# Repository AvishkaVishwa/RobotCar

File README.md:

# 🤖 Sumo Robot – ESP32 Upgrade Edition

> ⚡ A complete redesign and performance upgrade of my original ESP32-based 2-wheel robot — now featuring 4-wheel differential drive, dual motor drivers, enhanced sensing, and a **custom-designed 2-layer PCB** for clean, robust competition performance.

---
## 🏅 Awards & Achievements

> 🥈 **2nd Place – University Robotics Competition**  
> My previous 2-wheel ESP32-based robot won **2nd place** in a university competition.  
> 🎯 **Challenge Objective:** Remove the maximum number of boxes from a designated area as fast as possible.  
> 💡 The robot autonomously navigated, detected, and pushed objects while avoiding boundaries.  
>
> This new 4-wheel version builds on that success with:
> - A custom PCB for higher stability and motor control
> - Dual-mode (Autonomous + BLE Manual) operation
> - Improved PD-based line tracking and obstacle avoidance
> - Real-time scanning with servo-driven sensors

## 🔄 Evolution of the Project

| Original Prototype                    | 🚀 **Upgraded Version**                             |
|--------------------------------------|----------------------------------------------------|
| ESP32 on protoboard                  | ESP32 DevKit (38-pin) on custom 2-layer PCB        |
| 2-wheel drive with single TB6612FNG  | 4-wheel drive using dual TB6612FNG drivers         |
| Breadboard wiring                    | Professionally routed and labeled PCB in KiCad     |
| 1 ultrasonic + 2 IR sensors          | 2 ultrasonic + 3 IR sensors                        |
| Basic C firmware                     | Modular, RTOS-based firmware with **ESP-IDF**      |

### 🔧 The Current design 

| Old Design |
|------------|

---

## ⚙ Hardware Overview

### 📍 ESP32 GPIO Mapping

| Feature             | GPIOs                            | Description                      |
|---------------------|-----------------------------------|----------------------------------|
| **Motor Driver 1**  | AIN1: 13, AIN2: 14                | Left Front Motor Direction       |
|                     | BIN1: 12, BIN2: 27                | Left Rear Motor Direction        |
|                     | PWMA: 26, PWMB: 25                | Speed Control (PWM)              |
| **Motor Driver 2**  | AIN1: 33, AIN2: 32                | Right Front Motor Direction      |
|                     | BIN1: 19, BIN2: 18                | Right Rear Motor Direction       |
|                     | PWMA: 23, PWMB: 22                | Speed Control (PWM)              |
| **STBY Pin**        | 15                                | Keep HIGH to enable motors       |
| **IR Sensors**      | 34, 35, 39                        | Left, Center, Right (input only) |
| **Ultrasonic**      | TRIG1: 5, ECHO1: 36               | Front sensor                     |
|                     | TRIG2: 4, ECHO2: 21               | Side sensor                      |
| **Servos**          | SERVO1: 2, SERVO2: 17             | Optional (PWM outputs)           |

---

## 📐 PCB Design (KiCad)

This upgrade features a fully custom 2-layer PCB:
- Dual motor driver breakout with decoupling capacitors
- LM2596 buck converter (12V to 5V)
- Pull-up/pull-down resistors for boot-safe ESP32 pins
- Clear silk labels for servo, IR, ultrasonic, and power pins

### PCB Gallery

#### 📘 Schematic View

#### 🧵 Routed View

#### 📐 2D Top View

#### 🧱 3D Render

---

## ⚙ Software Architecture

Built using **ESP-IDF + FreeRTOS**, the firmware is modular and real-time.

| Module           | Function                                      |
|------------------|-----------------------------------------------|
|    `main.c`      | Set motor direction and PWM speed             |
|                  | Read ultrasonic and IR sensor values          |
|                  | Control servo angles (expandable feature)     |
|                  | Main loop with attack, avoid, search routines |

---

## 🔧 Setup & Flashing

### Prerequisites
- ESP-IDF environment
- ESP32 DevKit (38-pin)
- 12V battery + USB cable

### Flash Instructions

git clone https://github.com/AvishkaVishwa/RobotCar.git
cd robot-project
idf.py build
idf.py -p /dev/ttyUSB0 flash
idf.py monitor

---

## 📹 Videos & Demos

> 🎥 Want to see it in action?
> I’ve recorded videos of both the prototype and the upgraded robot performing edge detection, object pushing, and spiral search.

📌  <video src ="https://github.com/user-attachments/assets/8567fc42-a18b-4fbb-b69a-60d1c5493e56"></video>

📌 Here Is a test of the car with New PCB, I m still doing some modifications to this....😁 And i'm controlling the car with Bluetooth using the mobile phone.
    <video src ="https://github.com/user-attachments/assets/c9dc8e6a-7c8a-46cb-9330-15c2b81f15a4"></video>
---

## 📚 What This Project Shows

* Embedded firmware development with **ESP-IDF**
* **Custom PCB design** (routing, power, protection, labeling)
* Real-time autonomous behavior
* Motor control using **PWM & H-bridges**
* Sensor fusion: ultrasonic + IR edge detection
* Full-stack development from electronics to software

---

## 🤝 Contributions Welcome

Feel free to fork or suggest ideas such as:

* PID control integration
* Remote control override via WiFi
* OLED display for system status

---
---

## 🎉 Special Thanks to PCBWay

<p align="center">
  
</p>

I would like to give a huge shoutout and sincere thanks to **[PCBWay](https://www.pcbway.com/)** for sponsoring the PCB fabrication of this project!

The **build quality, silkscreen clarity, via precision, and copper finish** exceeded expectations. PCBWay’s service was fast, professional, and extremely helpful throughout the production process.

This project wouldn’t have been possible without their generous support. If you’re looking to manufacture professional-grade PCBs at an affordable price, I highly recommend checking them out.

🔗 [Visit PCBWay →](https://www.pcbway.com/)

---

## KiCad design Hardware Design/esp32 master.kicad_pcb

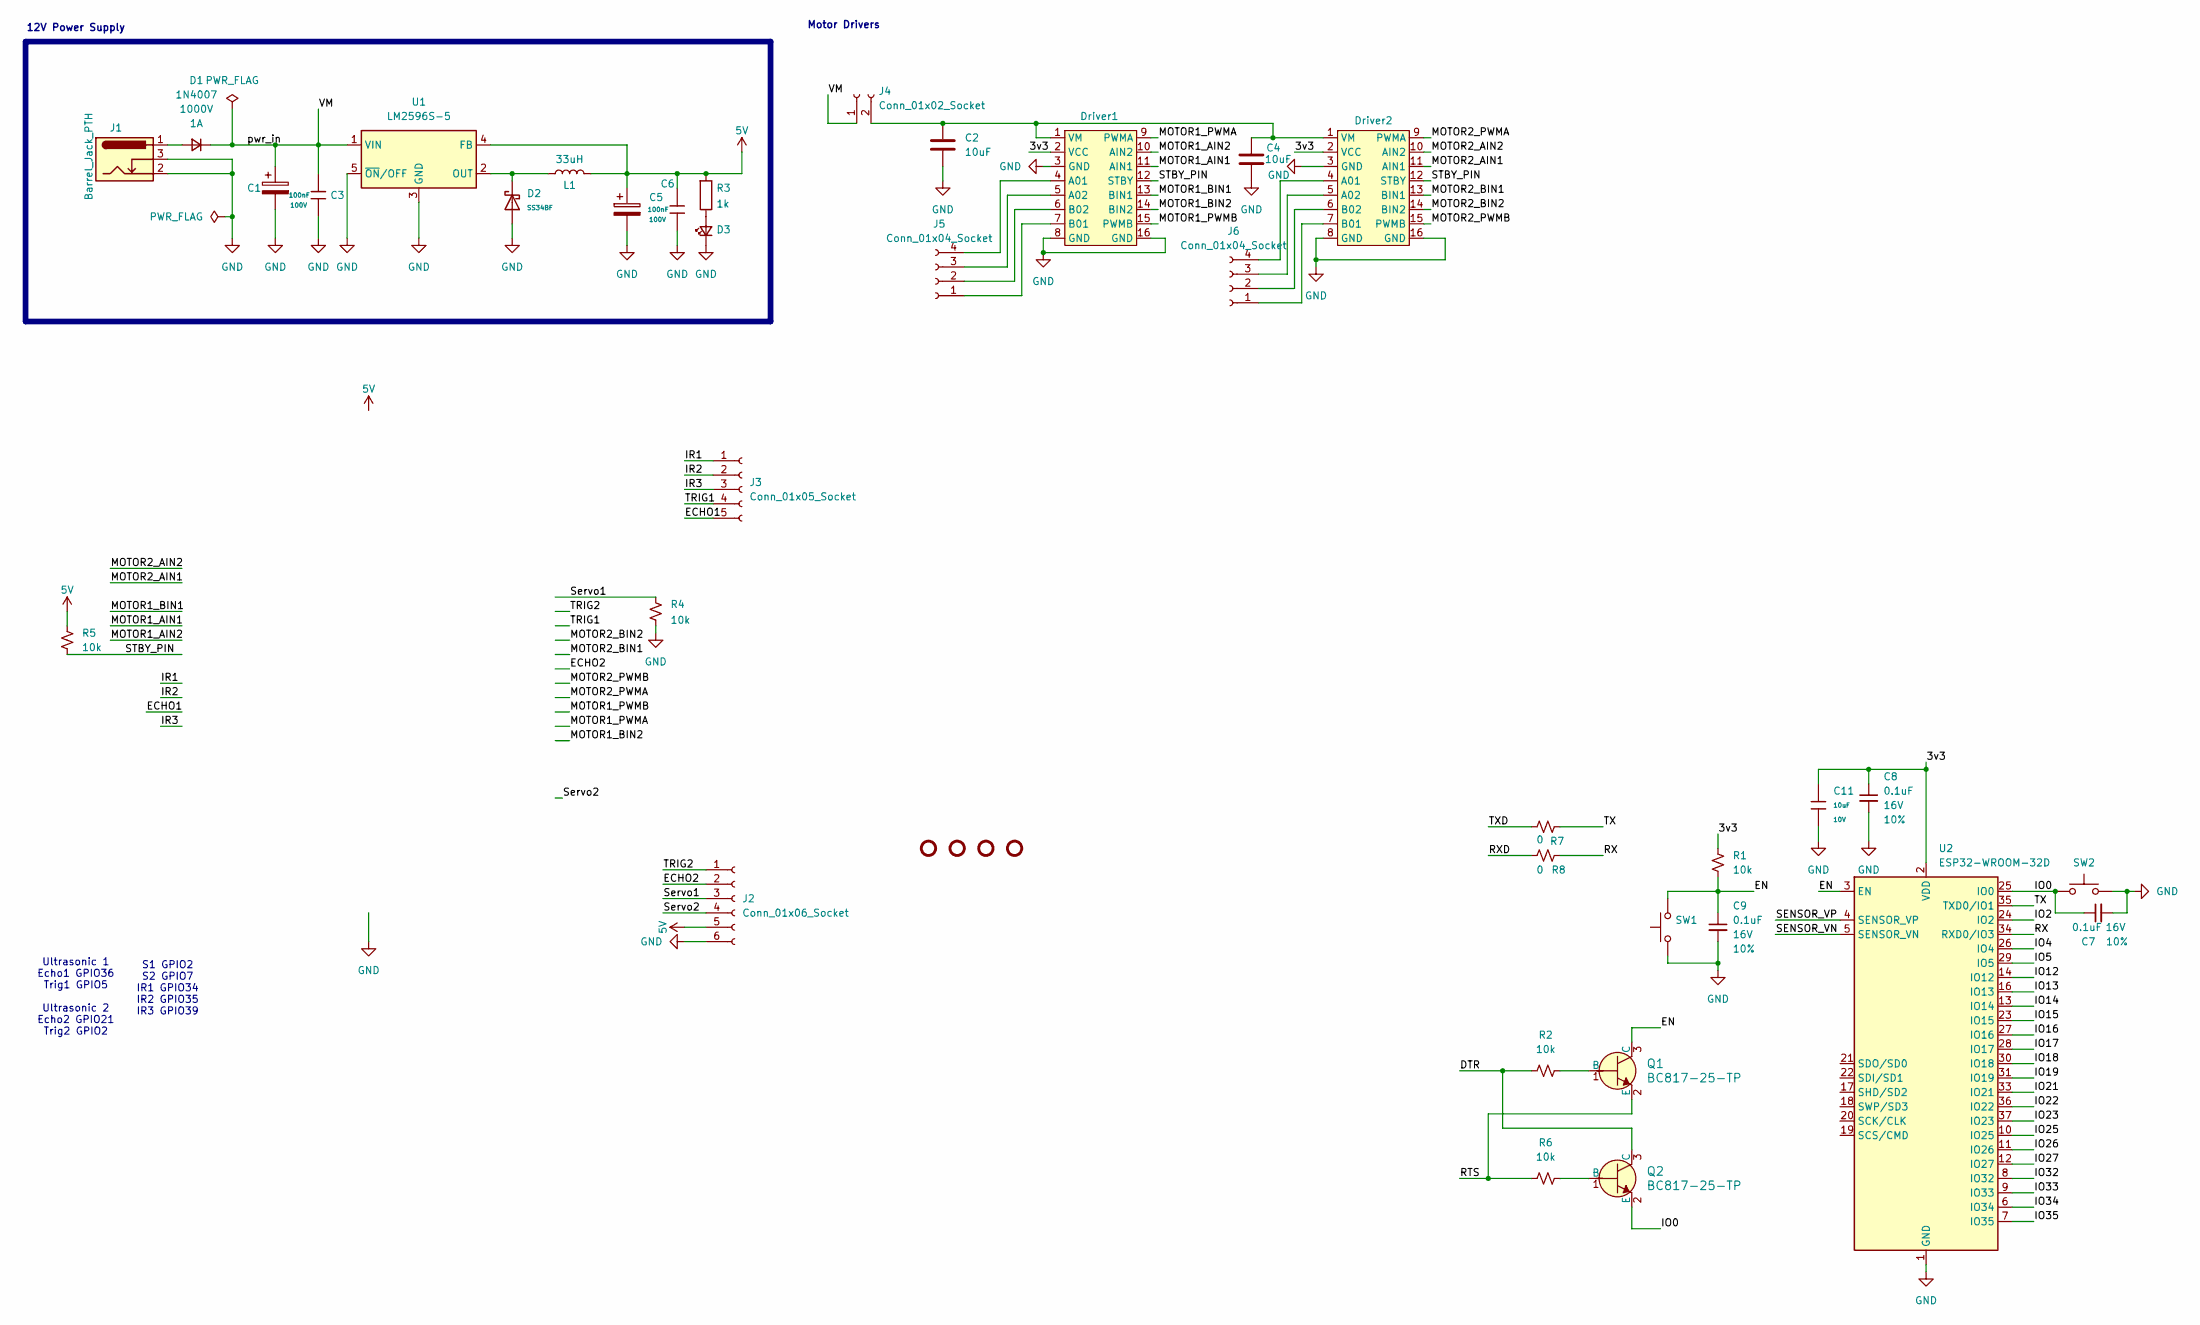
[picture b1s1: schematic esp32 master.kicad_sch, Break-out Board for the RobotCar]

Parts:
C1: CP_Radial_D8.0mm_P3.50mm; CP_Radial_D8.0mm_P2.50mm
C2, C4: 10uF; C_Radial_D6.3mm_H7.0mm_P2.50mm
C3, C6: 100nF; C_0805_2012Metric_Pad1.18x1.45mm_HandSolder; Voltage Rated 100V; Tolerance ±10%; Part CL21B104KCFNNNE; LCSC C28233
C5: CP_Radial_D8.0mm_P3.50mm; CP_Elec_6.3x5.4_Nichicon
C7, C8, C9: 0.1uF; C_0402_1005Metric; Voltage 16V; Tolerance 10%
C11: 10uF; C_0603; Voltage Rated 10V; Tolerance ±10%; Part CL10A106KP8NNNC; LCSC C19702
D1: 1N4007; D_A-405_P7.62mm_Horizontal
D2: SS34BF; D_SMBF; Voltage - DC Reverse(Vr) 40V; Part SS34BF; LCSC C42371739
D3: Yellow; LED_0603_1608Metric_Pad1.05x0.95mm_HandSolder
Driver1, Driver2: DIP-16_591_ELL
J1: Barrel_Jack_PTH; BarrelJack_Horizontal
J2: Conn_01x06_Socket; PinHeader_1x06_P2.54mm_Vertical
J3: Conn_01x05_Socket; PinHeader_1x05_P2.54mm_Vertical
J4: Conn_01x02_Socket; PinHeader_1x02_P2.54mm_Vertical
J5: Conn_01x04_Socket; PinHeader_1x04_P2.54mm_Vertical
J6: Conn_01x04_Socket; JST_EH_B4B-EH-A_1x04_P2.50mm_Vertical
L1: 33uH; L_12x12mm_H6mm
Q1, Q2: BC817-25-TP; SOT-23-3; MPN BC817-25-TP; Digi-Key_PN BC817-25-TPMSCT-ND
R1, R2, R4, R5, R6: 10k; R_0603_1608Metric
R3: 1k; R_0805_2012Metric_Pad1.20x1.40mm_HandSolder
R7, R8: 0; R_0603_1608Metric
ST1, ST2, ST3, ST4: Standoff
SW1, SW2: SMD_5.2x5.2mm_h1.9mm; Push_SMD_5.2x5.2mm_h1.9mm
U1: LM2596S-5; TO-263-5_TabPin3
U2: ESP32-WROOM-32D

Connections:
5V: C5.1, C6.1, J2.5, L1.2, R3.1, R5.2, U1.4 (FB)
/3v3: C8.1, C11.1, Driver1.2 (VCC), Driver2.2 (VCC), R1.2, U2.2 (VDD)
/DTR: Q2.3 (C), R2.2
/ECHO1: J3.5
/ECHO2: J2.2
/EN: C9.1, Q1.3 (C), R1.1, SW1.2, U2.3 (EN)
/IO0: C7.1, Q2.2 (E), SW2.1, U2.25 (IO0)
/IO2: U2.24 (IO2)
/IO4: U2.26 (IO4)
/IO5: U2.29 (IO5)
/IO12: U2.14 (IO12)
/IO13: U2.16 (IO13)
/IO14: U2.13 (IO14)
/IO15: U2.23 (IO15)
/IO16: U2.27 (IO16)
/IO17: U2.28 (IO17)
/IO18: U2.30 (IO18)
/IO19: U2.31 (IO19)
/IO21: U2.33 (IO21)
/IO22: U2.36 (IO22)
/IO23: U2.37 (IO23)
/IO25: U2.10 (IO25)
/IO26: U2.11 (IO26)
/IO27: U2.12 (IO27)
/IO32: U2.8 (IO32)
/IO33: U2.9 (IO33)
/IO34: U2.6 (IO34)
/IO35: U2.7 (IO35)
/IR1: J3.1
/IR2: J3.2
/IR3: J3.3
/MOTOR1_AIN1: Driver1.11 (AIN1)
/MOTOR1_AIN2: Driver1.10 (AIN2)
/MOTOR1_BIN1: Driver1.13 (BIN1)
/MOTOR1_BIN2: Driver1.14 (BIN2)
/MOTOR1_PWMA: Driver1.9 (PWMA)
/MOTOR1_PWMB: Driver1.15 (PWMB)
/MOTOR2_AIN1: Driver2.11 (AIN1)
/MOTOR2_AIN2: Driver2.10 (AIN2)
/MOTOR2_BIN1: Driver2.13 (BIN1)
/MOTOR2_BIN2: Driver2.14 (BIN2)
/MOTOR2_PWMA: Driver2.9 (PWMA)
/MOTOR2_PWMB: Driver2.15 (PWMB)
/RTS: Q1.2 (E), R6.2
/RX: R8.2, U2.34 (RXD0/IO3)
/RXD: R8.1
/SENSOR_VN: U2.5 (SENSOR_VN)
/SENSOR_VP: U2.4 (SENSOR_VP)
/STBY_PIN: Driver1.12 (STBY), Driver2.12 (STBY), R5.1
/Servo1: J2.3, R4.2
/Servo2: J2.4
/TRIG1: J3.4
/TRIG2: J2.1
/TX: R7.2, U2.35 (TXD0/IO1)
/TXD: R7.1
/VM: C1.1, C3.1, D1.1 (K), J4.1, U1.1 (VIN)
GND: C1.2, C2.2, C3.2, C4.2, C5.2, C6.2, C7.2, C8.2, C9.2, C11.2, D2.2, D3.1 (K), Driver1.3 (GND), Driver1.8 (GND), Driver1.16 (GND), Driver2.3 (GND), Driver2.8 (GND), Driver2.16 (GND), J1.2 (GND), J1.3 (GNDBREAK), J2.6, R4.1, SW1.1, SW2.2, U1.3 (GND), U1.5 (~ON/OFF), U2.1 (GND), U2.15 (GND), U2.38 (GND), U2.39 (GND)
unnamed: D1.2 (A), J1.1 (PWR)
unnamed: D3.2 (A), R3.2
unnamed: Driver1.4 (A01), J5.4
unnamed: Driver1.5 (A02), J5.3
unnamed: Driver1.7 (B01), J5.1
unnamed: Driver1.6 (B02), J5.2
unnamed: C2.1, C4.1, Driver1.1 (VM), Driver2.1 (VM), J4.2
unnamed: Driver2.4 (A01), J6.4
unnamed: Driver2.5 (A02), J6.3
unnamed: Driver2.7 (B01), J6.1
unnamed: Driver2.6 (B02), J6.2
unnamed: Q1.1 (B), R2.1
unnamed: Q2.1 (B), R6.1
unnamed: D2.1, L1.1, U1.2 (OUT)

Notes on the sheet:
S1 GPIO2 S2 GPIO7 IR1 GPIO34 IR2 GPIO35 IR3 GPIO39
12V Power Supply
Motor Drivers
Ultrasonic 1 Echo1 GPIO36 Trig1 GPIO5 Ultrasonic 2 Echo2 GPIO21 Trig2 GPIO2

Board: 4 copper layers, 40 parts (0 on the bottom side), 26 nets, no tracks yet.

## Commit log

2024-12-13 Add motor control and sensor integration for robot navigation
2024-12-14 Add images of hardware setup to README.md
2024-12-17 Enhance robot navigation with improved sensor integration and motor control
2025-05-20 Refactor code structure for improved readability and maintainability
2025-05-21 Remove unnecessary blank line at the beginning of README.md
2025-05-21 Refactor hardware design files and update README for clarity
2025-05-21 Revise README.md for clarity and detail in ESP32 upgrade, enhancing hardware overview and software architecture sections
2025-05-21 Remove introductory line from README.md to streamline content presentation
2025-05-21 Remove unnecessary markdown code block from README.md for clarity
2025-05-21 Update README.md to simplify the design comparison section by removing the new design column
2025-05-21 Update README.md to reflect current design changes and replace schematic image with updated version
2025-05-21 Update README.md to replace schematic images with new versions for improved clarity
2025-05-21 Update README.md to replace PCB top layout image with a new version for improved clarity
2025-05-21 Update README.md to add detailed project achievements and enhancements; add VSCode configuration files for improved development setup
2025-05-21 Update settings.json to specify cmake source directory; mark subproject as dirty
2025-05-21 Mark subproject as dirty in TheRobotCar firmware
2025-05-21 Remove TheRobotCar subproject and update .gitignore to exclude Firmware directory
2025-05-21 Update README.md to embed video link for enhanced accessibility
2025-05-21 Update drill files and job configuration for esp32 breakout board
    - Updated creation dates in NPTH and PTH drill files to 2025-05-21.
    - Adjusted coordinates in PTH drill file for improved accuracy.
    - Modified creation date in job configuration file to match the latest updates.
    - Added a new image to the README for better documentation.
    - Generated a report file detailing the plotted Gerber files for the breakout board.
2025-05-21 Update clone URL in flash instructions to point to the correct repository
2025-05-21 Refactor module function descriptions in README.md for clarity
2025-06-12 Update image reference in README.md and add new photo asset
2025-06-12 Add Car.mp4 asset to the project
2025-06-12 Update README.md to clarify Bluetooth control feature for car testing
2025-06-13 Add initial KiCad project files for car design
